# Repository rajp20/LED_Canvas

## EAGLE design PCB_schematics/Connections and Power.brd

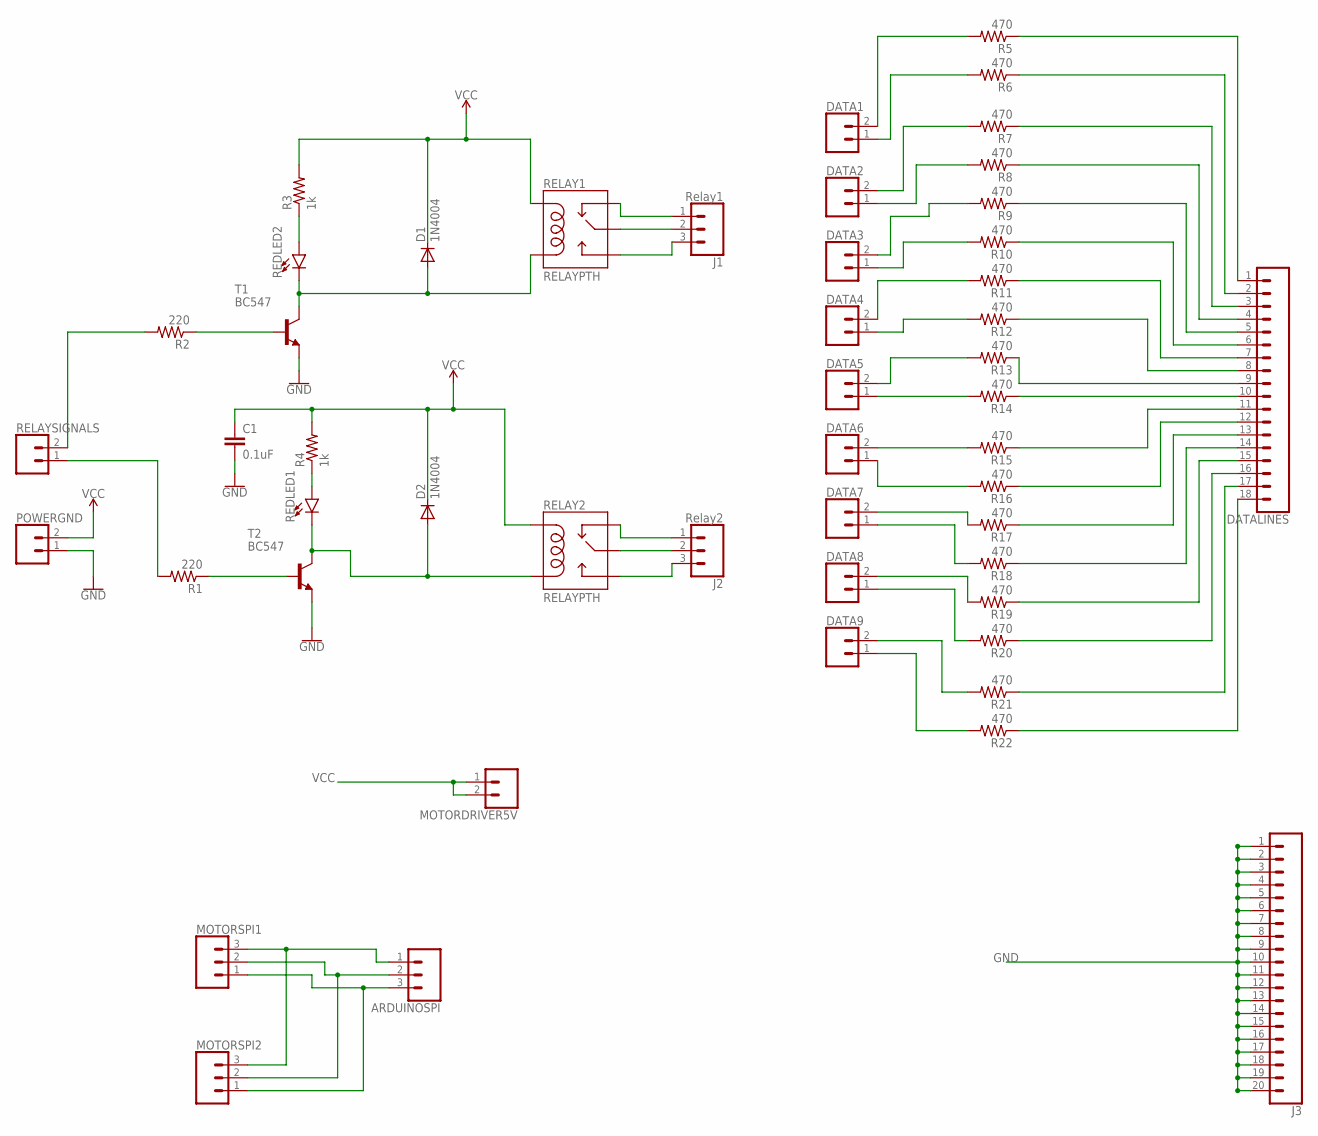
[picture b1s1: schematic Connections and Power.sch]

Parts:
ARDUINOSPI: CONN_03; 1X03
C1: 0.1uF; CAP-PTH-SMALL-KIT
D1, D2: 1N4004; DO41-10
DATA1, DATA2, DATA3, DATA4, DATA5, DATA6, DATA7, DATA8, DATA9: CONN_023.5MM; SCREWTERMINAL-3.5MM-2
DATALINES: CONN_18; 1X18
J1: Relay1; SCREWTERMINAL-5MM-3
J2: Relay2; SCREWTERMINAL-5MM-3
J3: CONN_20; 1X20
MOTORDRIVER5V: CONN_02; 1X02
MOTORSPI1, MOTORSPI2: CONN_03; 1X03
POWERGND: CONN_025MM; SCREWTERMINAL-5MM-2
R1, R2: 220; 0309/12
R3, R4: 1k; 0309/12
R5, R6, R7, R8, R9, R10, R11, R12, R13, R14, R15, R16, R17, R18, R19, R20, R21, R22: 470; 0309/12
REDLED1, REDLED2: LED1206; LED-1206
RELAY1, RELAY2: RELAYPTH; SRD-05VDC-SL-C
RELAYSIGNALS: CONN_025MM; SCREWTERMINAL-5MM-2
T1, T2: BC547; TO92

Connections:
GND: C1.2, J3.1, J3.2, J3.3, J3.4, J3.5, J3.6, J3.7, J3.8, J3.9, J3.10, J3.11, J3.12, J3.13, J3.14, J3.15, J3.16, J3.17, J3.18, J3.19, J3.20, POWERGND.1, T1.1 (E), T2.1 (E)
unnamed: DATA1.2, R5.2
unnamed: D2.A, REDLED1.C, RELAY2.COIL0, T2.3 (C)
unnamed: R4.1, REDLED1.A
unnamed: R2.2, RELAYSIGNALS.2
unnamed: J2.1, RELAY2.SWCLOSED (SWCLOSE)
unnamed: J2.2, RELAY2.SWCOMMON
unnamed: J2.3, RELAY2.SWOPEN
unnamed: R1.1, T2.2 (B)
unnamed: R2.1, T1.2 (B)
unnamed: D1.A, REDLED2.C, RELAY1.COIL0, T1.3 (C)
unnamed: R3.1, REDLED2.A
unnamed: DATA1.1, R6.2
unnamed: J1.1, RELAY1.SWCLOSED (SWCLOSE)
unnamed: J1.2, RELAY1.SWCOMMON
unnamed: J1.3, RELAY1.SWOPEN
unnamed: R1.2, RELAYSIGNALS.1
unnamed: DATA2.2, R7.2
unnamed: DATA2.1, R8.2
unnamed: DATA3.2, R9.2
unnamed: DATA3.1, R10.2
unnamed: DATA4.2, R11.2
unnamed: DATA4.1, R12.2
unnamed: DATA5.2, R13.2
unnamed: DATA5.1, R14.2
unnamed: DATA6.2, R15.2
unnamed: DATA6.1, R16.2
unnamed: DATA7.2, R17.2
unnamed: DATA7.1, R18.2
unnamed: DATA8.2, R19.2
unnamed: DATA8.1, R20.2
unnamed: DATA9.2, R21.2
unnamed: DATA9.1, R22.2
unnamed: DATALINES.18, R22.1
unnamed: DATALINES.17, R21.1
unnamed: DATALINES.16, R20.1
unnamed: DATALINES.15, R19.1
unnamed: DATALINES.14, R18.1
unnamed: DATALINES.13, R17.1
unnamed: DATALINES.12, R16.1
unnamed: DATALINES.11, R15.1
unnamed: DATALINES.10, R14.1
unnamed: DATALINES.1, R5.1
unnamed: DATALINES.2, R6.1
unnamed: DATALINES.3, R7.1
unnamed: DATALINES.4, R8.1
unnamed: DATALINES.5, R9.1
unnamed: DATALINES.6, R10.1
unnamed: DATALINES.7, R11.1
unnamed: DATALINES.8, R12.1
unnamed: DATALINES.9, R13.1
unnamed: ARDUINOSPI.1, MOTORSPI1.3, MOTORSPI2.3
unnamed: ARDUINOSPI.2, MOTORSPI1.2, MOTORSPI2.2
unnamed: ARDUINOSPI.3, MOTORSPI1.1, MOTORSPI2.1
VCC: C1.1, D1.C, D2.C, MOTORDRIVER5V.1, MOTORDRIVER5V.2, POWERGND.2, R3.2, R4.2, RELAY1.COIL1, RELAY2.COIL1

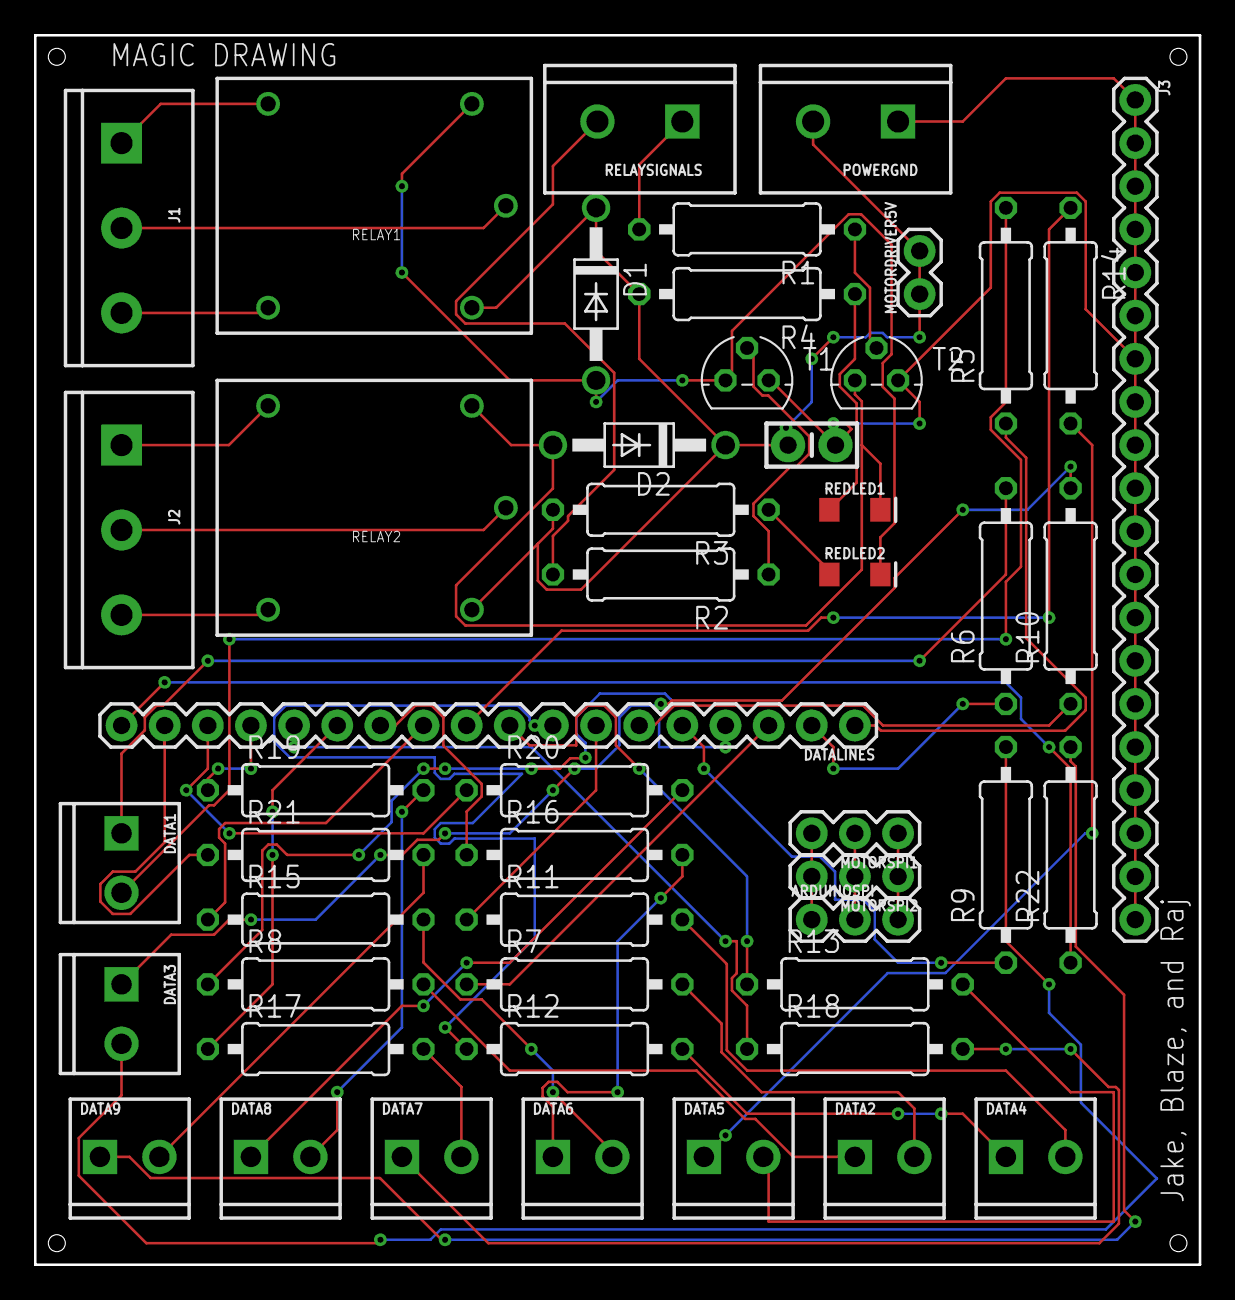
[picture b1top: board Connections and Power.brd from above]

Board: 2 copper layers, 68.6 x 72.4 mm, 50 parts (0 on the bottom side), 55 nets.

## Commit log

2018-09-13 Added Arduino project
2018-09-13 Created iOS app
2018-09-13 added gitignore
2018-09-18 added led controller
2018-09-18 test
2018-09-18 clean up
2018-09-18 Added four buttons to toggle colors of leds
2018-10-23 Drawing view controller (UARTModuleViewController) now draws line segments
2018-11-03 Drawing view added and working with skip button on main
2018-11-03 merged
2018-11-03 added controller for motor
2018-11-03 BT now sending data at full capacity
2018-11-06 added 18 led strip config
2018-11-06 Began the bouncing ball program.
2018-11-09 Started bouncing ball code.
2018-11-09 Added basic motor code.
2018-11-09 updated ble
2018-11-11 Began making custom class for menu bar at bottom of screen. Currently unable to connect UICollectionView to custom class
2018-11-17 Custom MenuCell class added and has basic functionality. Now needs styling
2018-11-17 MenuCell's are formatted a bit more. Unable to get text to be displayed in them and unable to add constraints to cells.
2018-11-17 Created a generic Queue class to be used for fading the alpha values of points that have been previously drawn.
2018-11-18 RGB colors are now working for paint brush.
2018-11-19 Queue generic class functionality working. Fading pixels needs tweaking and will need to change Pixel class to Line class.
2018-11-20 Pixels are now fading on drawing view. May need touch ups later.
2018-11-22 added latex file
2018-11-22 added table for parts
2018-11-24 Custom menu bar is now visible to the UARTModuleViewController
2018-11-24 MenuBar and cells now populated and formatted
2018-11-25 Several ways in which MenuCell's can open options menu and will need to decide on one. Fixed clear button.
2018-11-25 working on motor class
2018-11-25 Created segue between UARTViewController and Color selction. Bugs exist between segue such as navigation bar disapears.
2018-11-25 Push before merging cell to master
2018-11-25 updated motor controller
2018-11-25 Color of brush is now changeable via ColorController
2018-11-26 added clear screen
2018-11-26 added 'resetting' screen to LED controller and added ability to send packet to the iOS app.
2018-11-26 csv parser fix
2018-11-26 Segues & corresponding view controllers added for Patterns and Filters
2018-11-26 updated latex doc to match google doc
2018-11-26 small edits to ColorController
2018-11-26 Minor changes to UI throughout controllers
2018-11-27 Updates to labels, MenuCell padding, and reset button
2018-11-27 Added action to reset button on touch event. Apply button returns to UARTModuleViewController from ColorController
2018-11-28 fixed welcome and reset screens and added rainbow pixel test
2018-11-29 Removed dots that appeared in line as it was fading out
2018-11-29 bug fixes
2018-11-30 added actuator stuff
2018-12-01 push
2018-12-02 updated final document to match IEEE format
2018-12-03 UI changes
2018-12-03 added led clearing
2018-12-03 Added viewDidAppear function to send connected signal to peripheral
2018-12-03 added callbacks
2018-12-03 Updated slider tints to change as user selects new color in CollerController
2018-12-03 Added Poster directory for all poster work
2018-12-03 motors calibrated
2018-12-03 Steps smoothly now.
2018-12-03 draw ball update
2018-12-03 Fixed draw ball I think.
2018-12-03 added call back for data input
2018-12-03 bouncing ball fix
2018-12-03 Random colors when wall are hit.
2018-12-04 basic parser for XYZ data.
2018-12-04 Resized canvas and beginning to create correct pixel locations to send.
2018-12-04 Pixel translation should be accurate now. Drawing prohibitied out of bounds from canvas.
2018-12-04 Fixed the boundaries with the app.
2018-12-04 updated LED controller
2018-12-04 Application crash on upload
2018-12-04 added poster
2018-12-05 Magic Drawing Poster done
2018-12-05 Two way communication now implemented. **BUG**: app and canvas freeze after some state
2018-12-05 push for merge
2018-12-05 Added images to the buttons in UARTModuleViewController
2018-12-05 AppIcon added
2018-12-05 Removed redundant image
2018-12-05 poster update
2018-12-05 Reset button works now.
2018-12-05 Pattern button for ball added
2018-12-05 bouncing ball push and cleaned up some memory
2018-12-05 added ripple effect
2018-12-05 added acid mode
2018-12-05 Updated commands, added pattern buttons, tweaked resets. Bug remains in reset
2018-12-05 commands changed
2018-12-06 Fixed double connection errors.
2018-12-06 New button for Life pattern
2018-12-06 Added conways life algo.
2018-12-06 bug fixes, added fade to ripple, change conway, and added motor movement
2018-12-06 trying to get motors to move smoothly
2018-12-06 motors working, added drawBox for pixels, and added fade for draw
2018-12-07 UI updates, button configurations in PatternController
2018-12-07 bug fixes and removed interrupts
2018-12-07 Began commenting some classes
2018-12-07 mostly done
2018-12-12 final commit of working app
2018-12-12 added web page archive
2018-12-12 small update"
2018-12-18 Switched the MEGA and UNO code to different directories.
2018-12-18 PCB schematic files.
2018-12-18 added skip button
2018-12-18 updated doc
2018-12-18 pic fix and typo

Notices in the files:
parts and their libraries:
SparkFun-Connectors: Licensing: Creative Commons ShareAlike 4.0 International - https://creativecommons.org/licenses/by-sa/4.0
